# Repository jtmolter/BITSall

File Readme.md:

# Balloon Iridium Telemetry System

## DEPRECATED
Now part of https://github.com/UMDBPP/command_module

## Overview
This payload functions with an Iridium 9603 on a RockBlock carrier board. BITS has flown in various forms starting with NS-75 and continuously since NS-79 (10+ at this point) Iridium communications provide tracking from launch to landing, allowing for retrival of exact coordinates when landing in an area with no cell coverage. Additionally, the payload has been used as a long range link to then send data via XBee to other payloads.

Documentation is currently WIP (but for real this time)

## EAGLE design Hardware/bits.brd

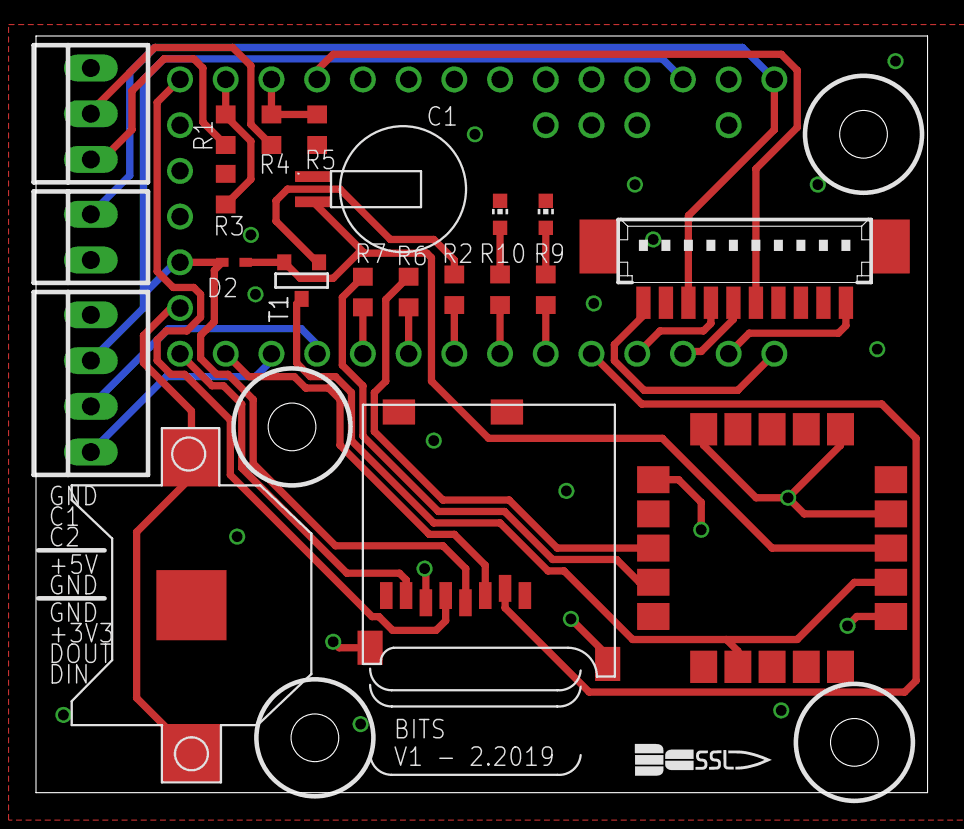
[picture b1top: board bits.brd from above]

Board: 2 copper layers, 49.5 x 42.0 mm, 23 parts (1 on the bottom side), 30 nets.

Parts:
C1: 0.2F elna supercap; ELNASUPERCAP
D2: RB520S30T1G; SOD523
IC1: SAM-M8Q
IMAG1: SSL.3IN_SILK; SSL_SILK_.3IN
LED1: Red; CHIP-LED0603
LED2: Green; CHIP-LED0603
R1, R4: 18k; R0603
R2: R0603
R3, R5: 10k; R0603
R6, R7: 22ohm; R0603
R9, R10: 470; R0603
T1: EnchancePchnlMOSFET; SOT-23
U$1: MICROSD
U$2: TEENSY_3.1-3.2_ALL_PINS; TEENSY_3.0-3.2&LC_ALL_PINS
U$3: CR1220SMT; CR1220-SMD
X1: 22-23-2021
X2: 53398-10
X3: 22-23-2031
X4: 22-23-2041

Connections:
+3V3: D2.A, U$1.4, U$2.3.3V, U$2.3.3V1, X4.3
+5V: U$2.VIN, X1.2, X2.8
BAT_CELL1: R1.2, R3.2, U$2.14/A0
BAT_CELL2: R4.1, R5.1, U$2.15/A1
CELL1: R1.1, X3.1
CELL2: R4.2, X3.2
DIN: U$2.10, X4.1
DOUT: U$2.9, X4.2
GND: C1.GND, IC1.1, IC1.4, IC1.5, IC1.6, IC1.10, IC1.11, IC1.15, IC1.16, IC1.20, LED1.C, LED2.C, R3.1, R5.2, U$1.6, U$1.MT1, U$1.MT2, U$2.GND, U$2.GND1, U$3.-, X1.1, X2.10, X3.3, X4.4
GPS3V3: C1.3V3, D2.C, IC1.3, T1.2
GPSON: R2.2, U$2.6
LED1: R9.1, U$2.4
LED2: R10.1, U$2.5
MISO: U$1.7, U$2.12
MOSI: U$1.3, U$2.11
unnamed: R2.1, T1.3
unnamed: LED2.A, R10.2
unnamed: LED1.A, R9.2
unnamed: IC1.14, R7.1
unnamed: IC1.13, R6.1
unnamed: IC1.2, IC1.17, T1.1
RING: U$2.16/A2, X2.5
RX3: R6.2, U$2.7
RXD: U$2.0, X2.1
SCK: U$1.5, U$2.13
SD_CS: U$1.2, U$2.3
SLEEP: U$2.2, X2.7
TX3: R7.2, U$2.8
TXD: U$2.1, X2.6
VBAT: U$2.VBAT, U$3.+$1, U$3.+$2

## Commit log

2019-04-02 First push of full v1 code
2019-04-09 Updated Back Forth Test Programs
2019-04-09 Updated XBee code on 2019v2
2019-04-16 Updating code post launch
2019-04-17 Added Helios passthrough
2019-04-26 Post flight crash prevention
2019-06-21 So many changes, I really should push more often
2019-06-21 More commenting
2019-06-30 Fix CS, timestamp problem resolve, echo on cmd rec
2019-07-04 GS update for NS-86, XBee optimization
2019-07-23 NS-86 mods and more fix attempts
2019-07-23 More edits, preparing for retest
2019-07-23 Fix readme
2019-07-29 Xbee on Init
2019-08-05 Fix log time because ints aren't strings
2019-10-09 Adding new revision
2019-10-09 File Sorting
2019-10-09 Rename Readme.txt to Readme.md
2019-10-09 Add logs, v4 test, logtime fix
2020-01-06 More Updates
2020-01-06 Flipped the GPS mosfet around
2020-01-06 Added value for gps Mosfet
2020-03-08 Created new directory for rev3 boards
2020-03-08 Preparing software for Boardrev3, documenting
